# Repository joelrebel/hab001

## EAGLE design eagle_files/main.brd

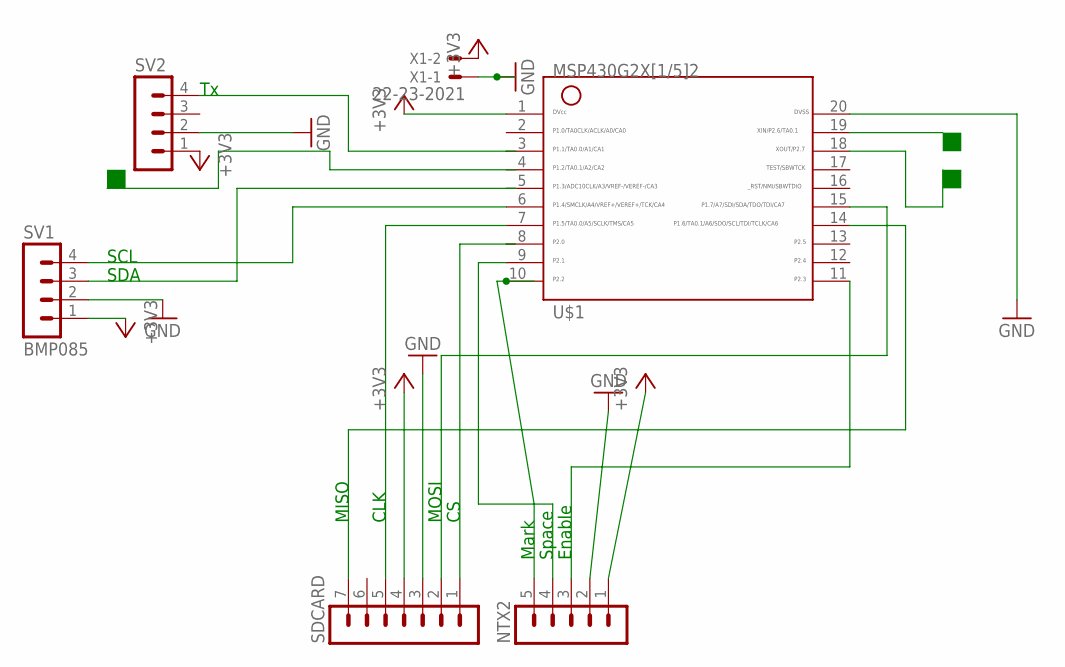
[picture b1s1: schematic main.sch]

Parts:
NTX2: MA05-1
SDCARD: MA07-1
SV1: BMP085; MA04-1
SV2: MA04-1
U$1: G2X[1/5]2---N20; N20
X1: 22-23-2021

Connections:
+3V3: NTX2.1, SDCARD.4, SV1.1, SV2.1, U$1.1, X1.2
GND: NTX2.2, SDCARD.3, SV1.2, SV2.2, U$1.20, X1.1
unnamed: SV1.4, U$1.6
unnamed: SV1.3, U$1.5
unnamed: SDCARD.1, U$1.8
unnamed: SDCARD.2, U$1.15
unnamed: SDCARD.5, U$1.7
unnamed: SDCARD.7, U$1.14
unnamed: SV2.4, U$1.3
unnamed: NTX2.5, U$1.10
unnamed: NTX2.3, U$1.11
unnamed: NTX2.4, U$1.9

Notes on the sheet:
SDA
SCL
Mark
Space
Enable
CLK
MOSI
MISO

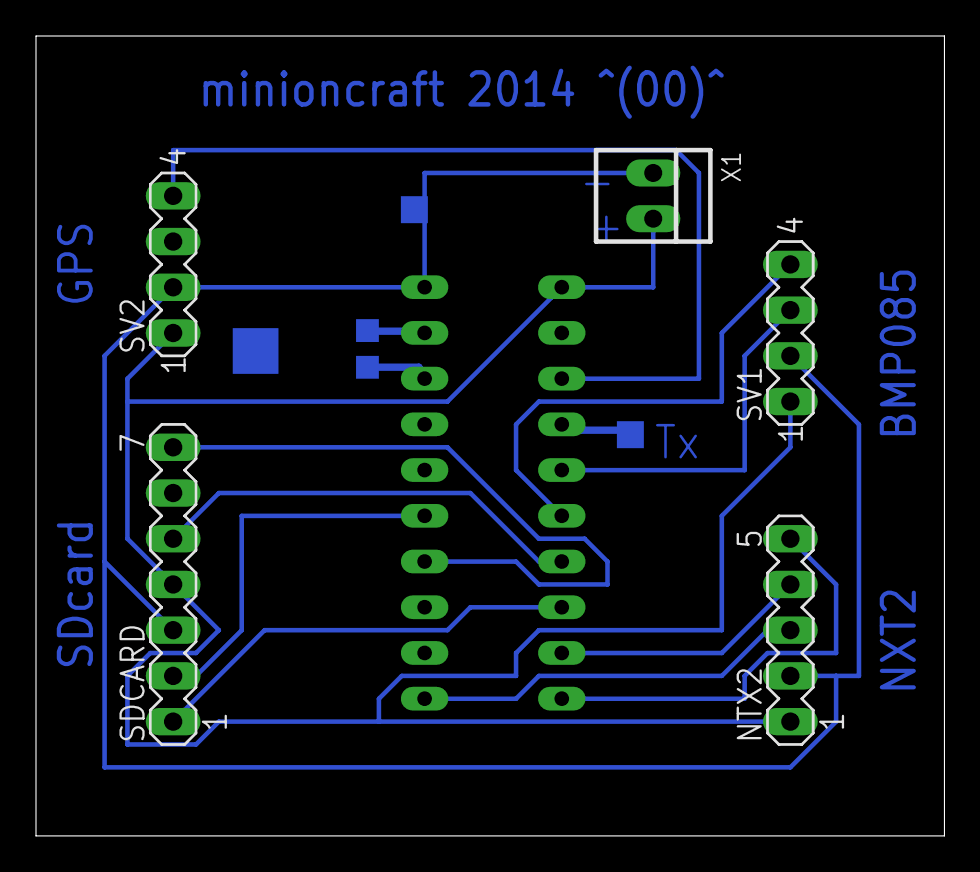
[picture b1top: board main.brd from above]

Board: 2 copper layers, 50.5 x 44.4 mm, 6 parts (1 on the bottom side), 12 nets.

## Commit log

2013-11-09 standardize to DELAY instead of _delay_ms
2013-11-09 fix baud
2013-11-09 missed out bits per char
2013-11-09 use a pointer
2013-11-09 define, fix prototype
2013-11-09 include itoa/atoi code; fix up sector handling; enable rtty
2013-11-09 add debugging symbols
2014-02-13 update connections doc
2014-02-13 minor fixes
2014-02-13 include files missed out earlier
2014-02-13 include eagle files for main board
2014-02-14 fix board design
2014-03-11 gitignore
2014-03-11 Add crc checks; include altitude, speed in knots, battery voltage stats; other minor fixes
2014-03-11 enable GPGSV, GPRMC messages
2014-03-11 specify power requirements
